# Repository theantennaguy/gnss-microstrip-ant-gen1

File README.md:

# gnss-microstrip-ant-gen1
This repository holds the design files, namely the PCB designs for building a GNSS microstrip antenna, one among others available on my GitHub.

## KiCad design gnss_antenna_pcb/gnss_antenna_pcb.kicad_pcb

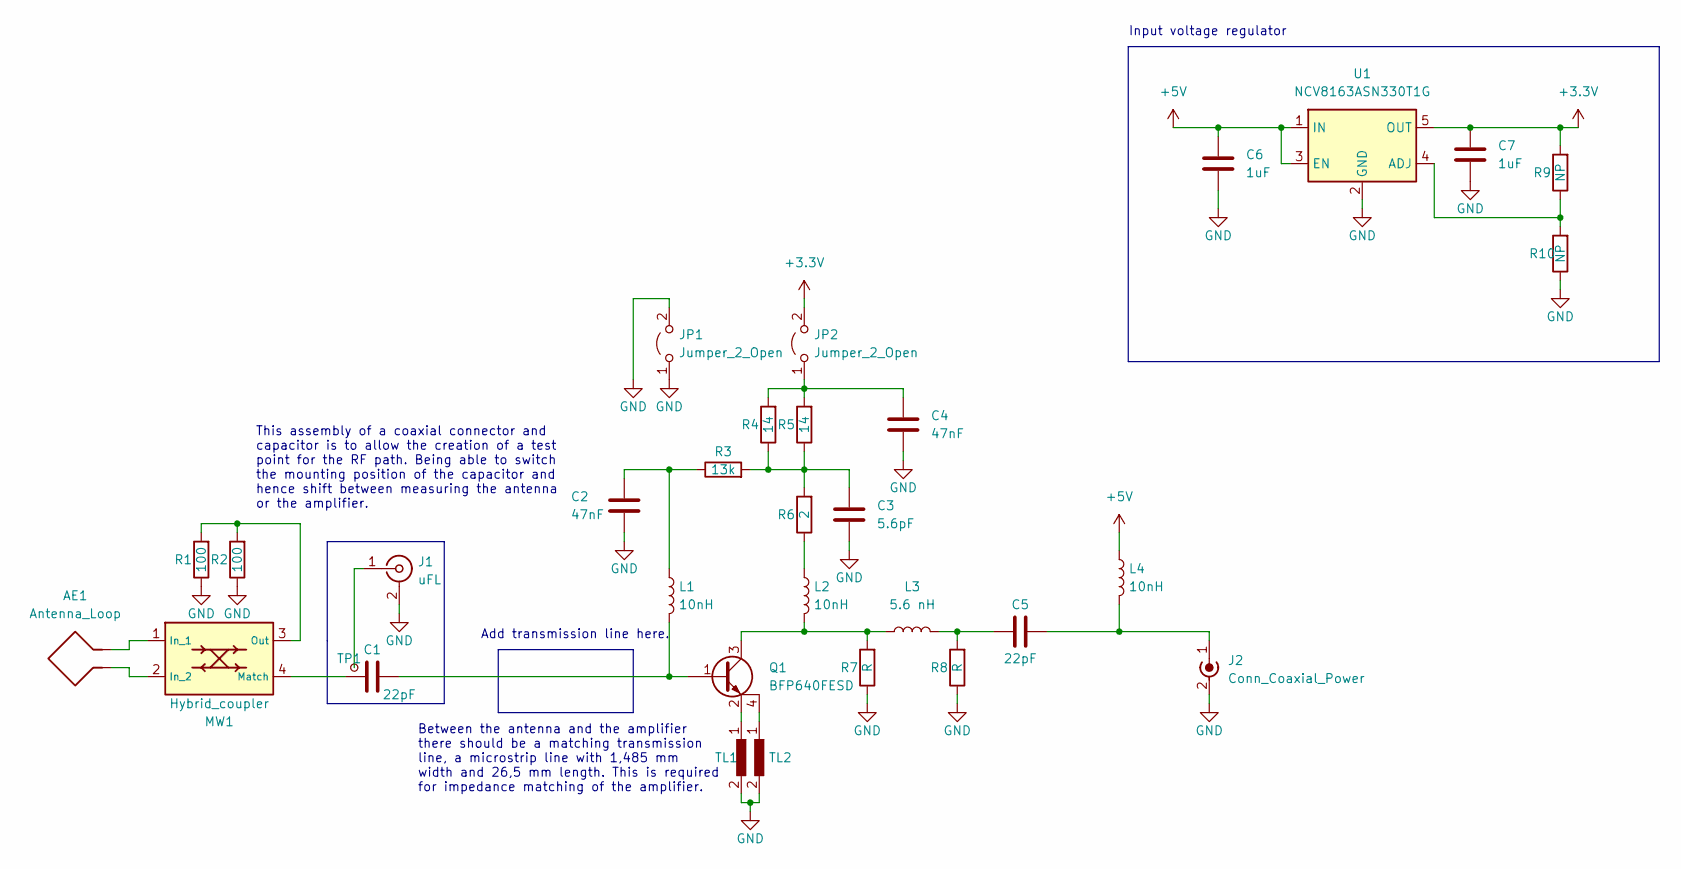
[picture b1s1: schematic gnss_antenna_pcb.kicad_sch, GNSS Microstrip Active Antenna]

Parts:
AE1: Antenna_Loop; ring_patch_feed-points
C1, C5: 22pF; C_0402_1005Metric_Pad0.74x0.62mm_HandSolder
C2, C4: 47nF; C_0603_1608Metric_Pad1.08x0.95mm_HandSolder
C3: 5.6pF; C_0402_1005Metric_Pad0.74x0.62mm_HandSolder
C6, C7: 1uF; C_0603_1608Metric_Pad1.08x0.95mm_HandSolder
J1: uFL; U.FL_Hirose_U.FL-R-SMT-1_Vertical
J2: Conn_Coaxial_Power; SMA_Molex_73251-1153_EdgeMount_Horizontal
JP1, JP2: Jumper_2_Open; PinHeader_1x02_P2.54mm_Vertical
L1, L2, L4: 10nH; L_0402_1005Metric
L3: 5.6 nH; L_0402_1005Metric_Pad0.77x0.64mm_HandSolder
MW1: Hybrid_coupler; hybrid_square_1.575ghz
Q1: BFP640FESD; BFP640FESDH6327
R1, R2: 100; R_0402_1005Metric_Pad0.72x0.64mm_HandSolder
R3: 13k; R_0603_1608Metric
R4, R5: 14; R_0603_1608Metric
R6: 2; R_0603_1608Metric
R7, R8: R; R_0402_1005Metric_Pad0.72x0.64mm_HandSolder
R9, R10: NP; R_0402_1005Metric_Pad0.72x0.64mm_HandSolder
TL1, TL2: Emiter_load_line; BFP640FESD_emitter_loadline
TP1: TestPoint_Small; TestPoint_Pad_1.0x1.0mm
U1: NCV8163ASN330T1G; TSOT-23-5

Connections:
+3.3V: C7.1, JP2.2 (B), R9.2, U1.5 (OUT)
+5V: C6.1, L4.1, U1.1 (IN), U1.3 (EN)
GND: C2.1, C3.2, C4.2, C6.2, C7.2, J1.2 (Ext), J2.2 (Ext), JP1.1 (A), JP1.2 (B), R1.1, R2.1, R7.1, R8.1, R10.1, TL1.2, TL2.2, U1.2 (GND)
unnamed: AE1.1, MW1.1 (In_1)
unnamed: AE1.2, MW1.2 (In_2)
unnamed: C1.1, MW1.4 (Match)
unnamed: C1.2, L1.2, Q1.1 (B)
unnamed: C2.2, L1.1, R3.1
unnamed: C3.1, R3.2, R4.1, R5.1, R6.2
unnamed: C4.1, JP2.1 (A), R4.2, R5.2
unnamed: C5.1, L3.2, R8.2
unnamed: C5.2, J2.1 (In), L4.2
unnamed: J1.1 (In), TP1.1
unnamed: L2.1, R6.1
unnamed: L2.2, L3.1, Q1.3 (C), R7.2
unnamed: MW1.3 (Out), R1.2, R2.2
unnamed: Q1.2 (E), TL1.1
unnamed: Q1.4 (E), TL2.1
unnamed: R9.1, R10.2, U1.4 (ADJ)

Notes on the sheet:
This assembly of a coaxial connector and capacitor is to allow the creation of a test point for the RF path. Being able to switch the mounting position of the capacitor and hence shift between measuring the antenna or the amplifier.
Between the antenna and the amplifier there should be a matching transmission line, a microstrip line with 1,485 mm width and 26,5 mm length. This is required for impedance matching of the amplifier.
Add transmission line here.
Input voltage regulator

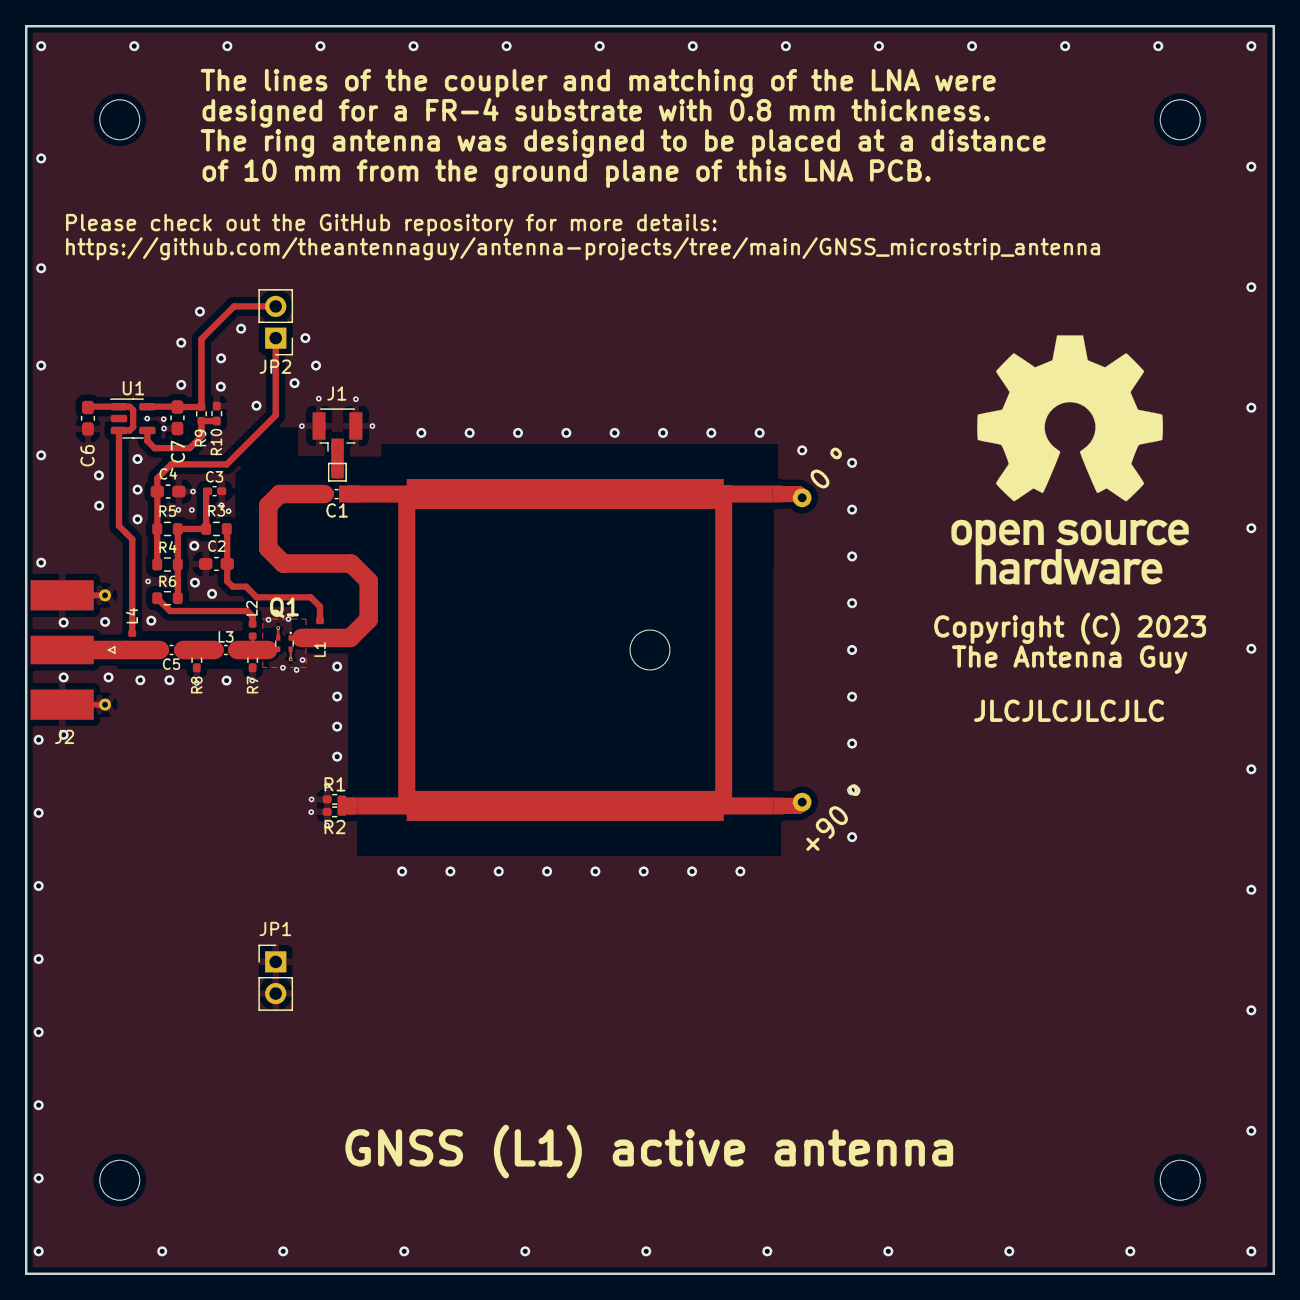
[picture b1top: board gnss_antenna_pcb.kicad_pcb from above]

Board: 2 copper layers, 100.0 x 100.0 mm, 32 parts (0 on the bottom side), 19 nets.

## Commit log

2023-01-17 Upload initial files
2023-01-17 Load license
2023-01-17 Update PCB
2023-01-18 Finish PCB + generate fabrication files
2023-01-21 Update PCB design + generate new fab files

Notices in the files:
gnss_antenna_pcb/gnss_antenna_pcb.kicad_pcb:
Copyright (C) 2023
